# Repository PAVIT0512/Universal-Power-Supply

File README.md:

# Universal Power Supply

## Introduction

A **Universal Power Supply** is an essential component in electronics, designed to convert alternating current (AC) from the mains into direct current (DC) for use in various electronic devices and systems. 🧩

Many electronic applications require different DC voltage levels, such as +5V, -5V, +12V, and -12V, to power components like microcontrollers, sensors, and communication modules. ⚙️ However, the power available from wall outlets is typically high-voltage AC (230V AC or 110V AC), depending on the region. Converting this high-voltage AC into stable, low-voltage DC is crucial for the safe and effective operation of electronic devices. 🔌

## Components

### Transformer
The transformer steps down the high-voltage AC from the mains to a lower, more manageable AC voltage. It also provides electrical isolation between the high-voltage input and the low-voltage output, enhancing safety. 🏠

### Rectifier
The rectifier converts the AC voltage from the transformer into pulsating DC. This process changes the alternating nature of AC to a unidirectional flow of current. The most common configuration is the bridge rectifier, which uses four diodes for full-wave rectification, efficiently utilizing the entire AC cycle. 🔄

### Capacitors
After rectification, the DC voltage still contains ripples. Filter capacitors smooth out these ripples, resulting in a more stable DC voltage. Large electrolytic capacitors are typically used for this purpose, complemented by smaller ceramic capacitors to filter out high-frequency noise. 🧪

### Voltage Regulators
Voltage regulators ensure the output DC voltages are stable and precise, regardless of variations in the input voltage or load conditions. Common regulators include:
- **7805**: Provides a stable +5V output.
- **7905**: Provides a stable -5V output.
- **7812**: Provides a stable +12V output.
- **7912**: Provides a stable -12V output. ⚙️

### Thermal Management
Heat sinks are often attached to the regulators to dissipate excess heat and maintain safe operating temperatures. 🌡️

## Summary

A Universal Power Supply is crucial for powering various electronic components and systems by converting high-voltage AC to stable, multi-level DC outputs. It simplifies the design of electronic systems, reduces the need for multiple power sources, and ensures reliable operation. 🛠️

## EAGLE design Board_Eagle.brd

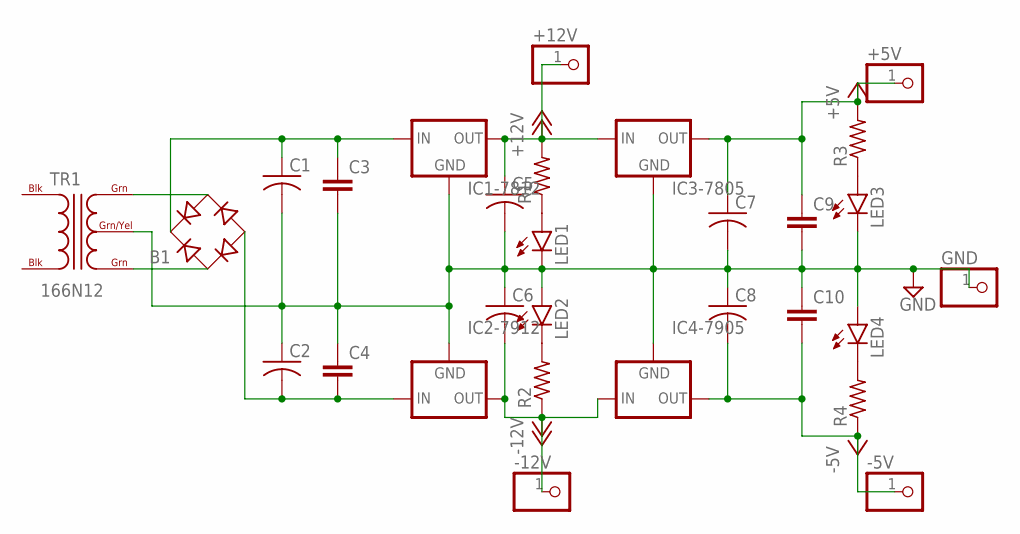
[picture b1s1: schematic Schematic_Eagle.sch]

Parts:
+5V, +12V: PINHD-1X1; 1X01
-5V, -12V: PINHD-1X1; 1X01
B1: RB1A
C1, C2, C5, C6, C7, C8: C-US025-025X050; C025-025X050
C3, C4, C9, C10: C-EU025-025X050; C025-025X050
GND: PINHD-1X1; 1X01
IC1-7812, IC3-7805: 78XXL
IC2-7912, IC4-7905: 79XXL
LED1, LED2, LED3, LED4: LED5MM
R1, R2, R3, R4: R-US_0204/7; 0204/7
TR1: 166N12; C13H

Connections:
+5V: +5V.1, C7.1, C9.1, IC3-7805.OUT, R3.2
+12V: +12V.1, C5.1, IC1-7812.OUT, IC3-7805.IN, R1.2
-5V: -5V.1, C8.2, C10.2, IC4-7905.OUT, R4.1
-12V: -12V.1, C6.2, IC2-7912.OUT, IC4-7905.IN, R2.1
GND: C1.2, C2.1, C3.2, C4.1, C5.2, C6.1, C7.2, C8.1, C9.2, C10.1, GND.1, IC1-7812.GND, IC2-7912.GND, IC3-7805.GND, IC4-7905.GND, LED1.K (C), LED2.A, LED3.K (C), LED4.A, TR1.GRN/YEL
unnamed: B1.AC1, TR1.GRN@2 (GRN)
unnamed: B1.AC2, TR1.GRN@1 (GRN)
unnamed: B1.+, C1.1, C3.1, IC1-7812.IN
unnamed: B1.-, C2.2, C4.2, IC2-7912.IN
unnamed: LED1.A, R1.1
unnamed: LED2.K (C), R2.2
unnamed: LED3.A, R3.1
unnamed: LED4.K (C), R4.2

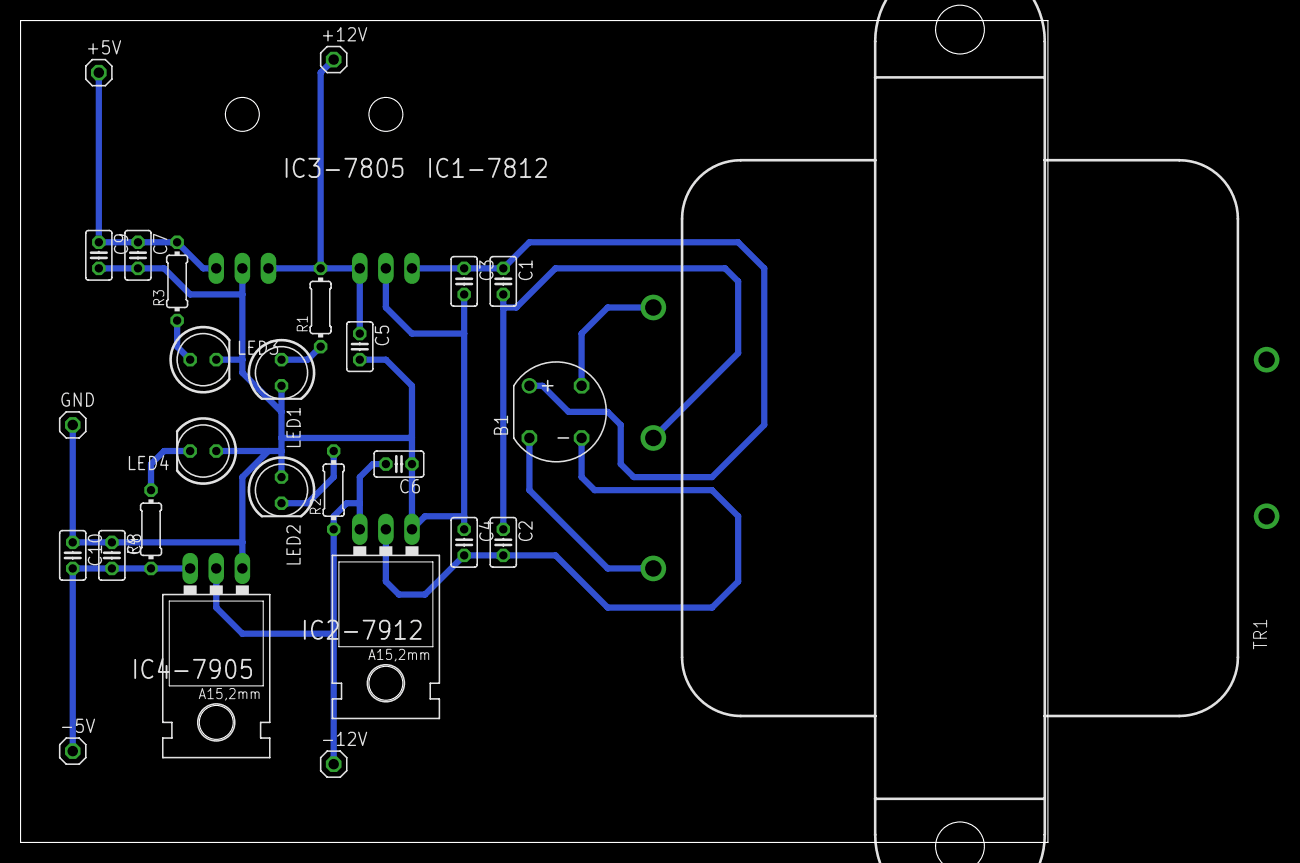
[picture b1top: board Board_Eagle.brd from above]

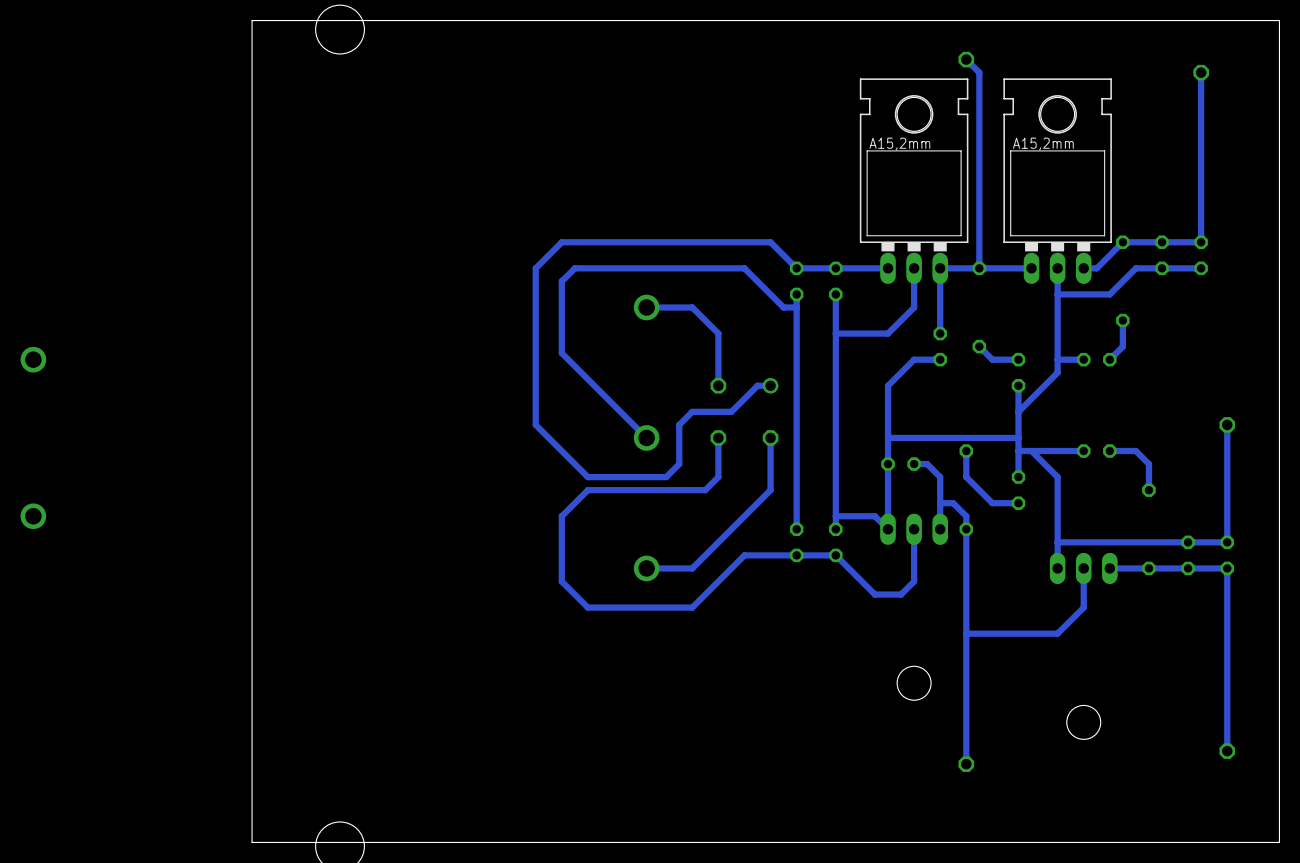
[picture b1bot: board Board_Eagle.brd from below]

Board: 2 copper layers, 100.0 x 80.0 mm, 29 parts (2 on the bottom side), 13 nets.
